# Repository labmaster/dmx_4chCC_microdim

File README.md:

# dmx_4chCC_microdim
very small 4 Channel DMX Constant Current Dimmer, max. 40V 350mA / channel,  Size 26mmx22mm, based on MY9942

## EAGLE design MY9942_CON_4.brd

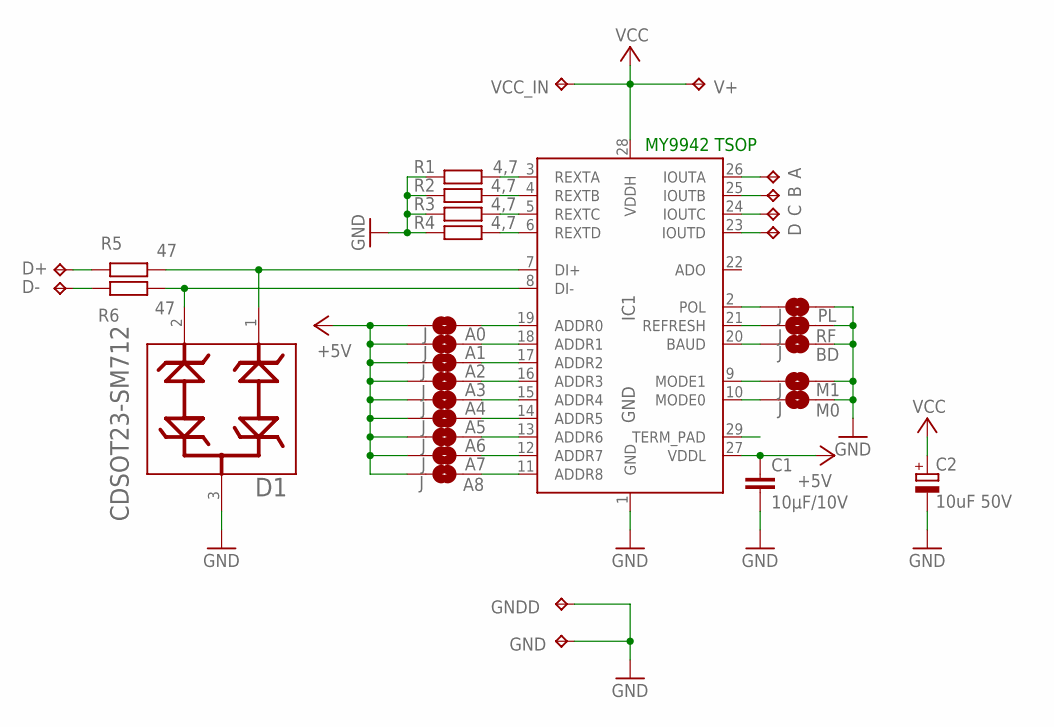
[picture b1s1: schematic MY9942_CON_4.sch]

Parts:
A: TPPAD1-13; P1-13
A0, A1, A2, A3, A4, A5, A6, A7, A8: J; SMT-JUMPER_2_NO_SILK
B: TPPAD1-13; P1-13
BD: J; SMT-JUMPER_2_NO_SILK
C: TPPAD1-13; P1-13
C1: 10µF/10V; C0805
C2: 10uF 50V; SMC_C
D: TPPAD1-13; P1-13
D1: SM712 / SOT23-3; BOURNS_INC._CDSOT23-SM712_0
D+: TPPAD1-13; P1-13
D-: TPPAD1-13; P1-13
GND: TPPAD1-13; P1-13
GNDD: TPPAD1-13; P1-13
IC1: GND; TSSOP28
M0, M1: J; SMT-JUMPER_2_NO_SILK
PL: J; SMT-JUMPER_2_NO_SILK
R1, R2, R3, R4: 4,7; R0805
R5, R6: 47; R0805
RF: J; SMT-JUMPER_2_NO_SILK
V+: TPPAD1-13; P1-13
VCC_IN: TPPAD1-13; P1-13

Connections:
+5V: A0.1, A1.1, A2.1, A3.1, A4.1, A5.1, A6.1, A7.1, A8.1, C1.1, IC1.27 (VDDL)
A: A.TP, IC1.26 (IOUTA)
B: B.TP, IC1.25 (IOUTB)
C: C.TP, IC1.24 (IOUTC)
D: D.TP, IC1.23 (IOUTD)
D+: D1.1, IC1.7 (DI+), R5.2
D-: D1.2, IC1.8 (DI-), R6.2
GND: BD.2, C1.2, C2.-, D1.3, GND.TP, GNDD.TP, IC1.1 (GND), M0.2, M1.2, PL.2, R1.1, R2.1, R3.1, R4.1, RF.2
unnamed: A8.2, IC1.11 (ADDR8)
unnamed: A7.2, IC1.12 (ADDR7)
unnamed: A6.2, IC1.13 (ADDR6)
unnamed: A5.2, IC1.14 (ADDR5)
unnamed: A4.2, IC1.15 (ADDR4)
unnamed: A3.2, IC1.16 (ADDR3)
unnamed: A2.2, IC1.17 (ADDR2)
unnamed: A1.2, IC1.18 (ADDR1)
unnamed: A0.2, IC1.19 (ADDR0)
unnamed: D+.TP, R5.1
unnamed: IC1.3 (REXTA), R1.2
unnamed: IC1.4 (REXTB), R2.2
unnamed: IC1.5 (REXTC), R3.2
unnamed: IC1.6 (REXTD), R4.2
unnamed: D-.TP, R6.1
unnamed: BD.1, IC1.20 (BAUD)
unnamed: IC1.9 (MODE1), M1.1
unnamed: IC1.10 (MODE0), M0.1
unnamed: IC1.21 (REFRESH), RF.1
unnamed: IC1.2 (POL), PL.1
TERM: IC1.29 (TERM_PAD)
VCC: C2.+, IC1.28 (VDDH), V+.TP, VCC_IN.TP

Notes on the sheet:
MY9942 TSOP

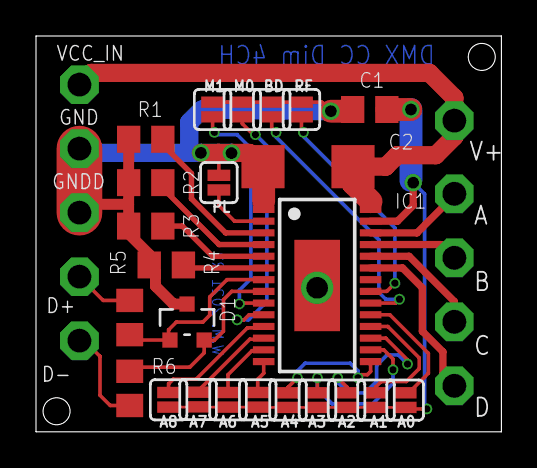
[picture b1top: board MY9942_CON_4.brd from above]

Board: 2 copper layers, 25.9 x 22.0 mm, 34 parts (0 on the bottom side), 29 nets.

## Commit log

2021-07-15 Add files via upload
    Eagle Files for board and schematic, PDF overview of board sides, BOM
2021-07-15 Add files via upload
    MY9942 datasheet , check this for choosing current setting resistors and correct solder jumper configuration

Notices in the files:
parts and their libraries:
SparkFun-Jumpers: Licensing: Creative Commons ShareAlike 4.0 International - https://creativecommons.org/licenses/by-sa/4.0
